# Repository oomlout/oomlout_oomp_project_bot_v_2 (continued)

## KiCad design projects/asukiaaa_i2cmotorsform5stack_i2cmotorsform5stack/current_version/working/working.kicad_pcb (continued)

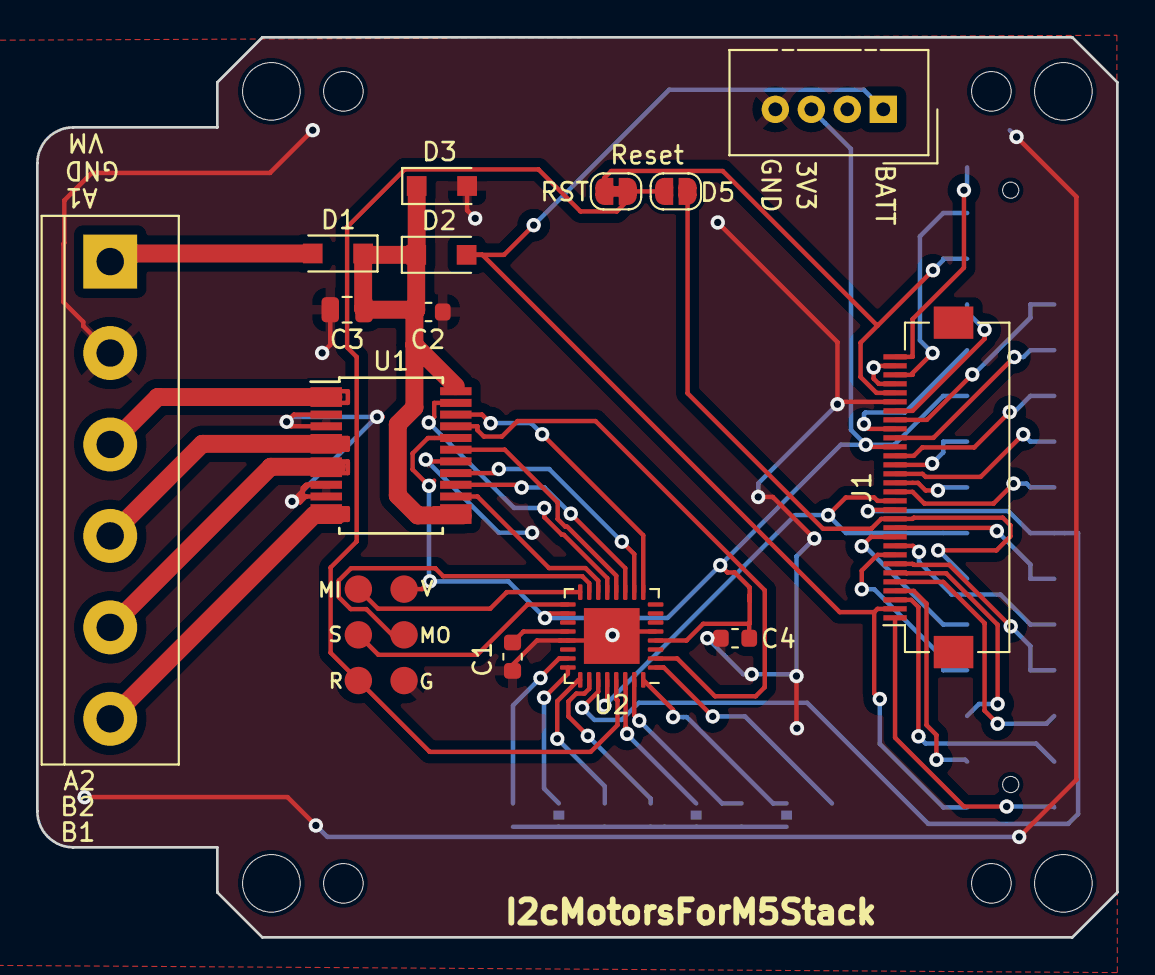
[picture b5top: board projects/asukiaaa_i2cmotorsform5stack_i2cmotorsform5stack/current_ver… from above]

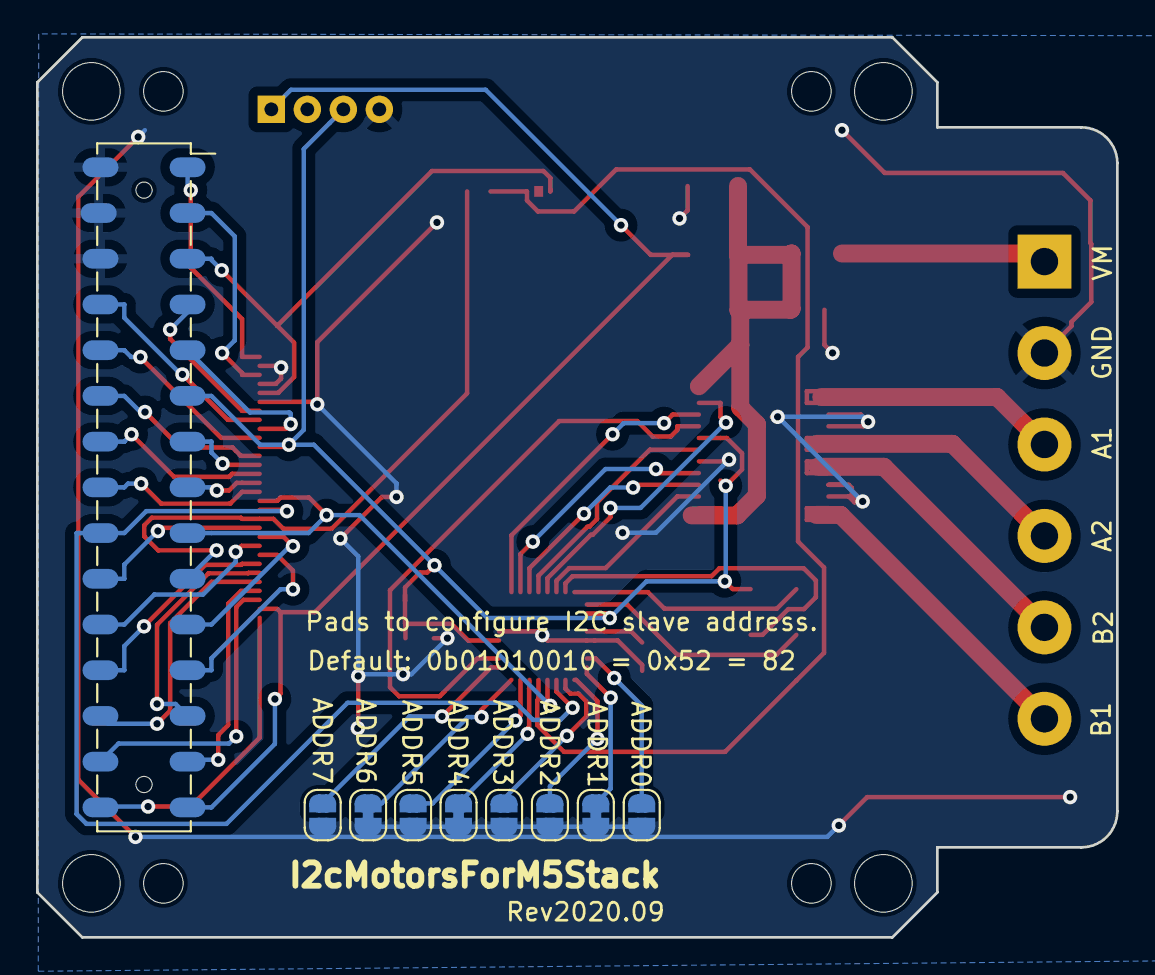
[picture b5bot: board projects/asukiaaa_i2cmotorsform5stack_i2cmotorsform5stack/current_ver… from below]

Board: 2 copper layers, 60.0 x 50.0 mm, 32 parts (9 on the bottom side), 54 nets.

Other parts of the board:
REF1, REF4, REF6, REF9: MountingHole_3.2mm_M3
REF2, REF3, REF7, REF8: MountingHole_2.2mm_M2

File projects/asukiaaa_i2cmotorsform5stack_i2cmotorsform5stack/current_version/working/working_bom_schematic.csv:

"Source:","C:\gh\oomlout_oomp_project_bot_v_2\projects\asukiaaa_i2cmotorsform5stack_i2cmotorsform5stack\current_version\working\working.kicad_sch"
"Date:","25/09/2023 20:22:21"
"Tool:","Eeschema 7.0.6"
"Generator:","C:/Program Files/KiCad/7.0/bin/scripting/plugins/bom_csv_grouped_by_value_with_fp.py"
"Component Count:","24"
"Ref","Qnty","Value","Cmp name","Footprint","Description","Vendor","DNP"
"ADDR0, ADDR2, ADDR3, ADDR5, ADDR7","5","NO","Jumper_NO_Small-Device-I2cMotorsForM5Stack-rescue","Jumper:SolderJumper-2_P1.3mm_Open_RoundedPad1.0x1.5mm","","",""
"ADDR1, ADDR4, ADDR6","3","NC","Jumper_NC_Small-Device-I2cMotorsForM5Stack-rescue","Jumper:SolderJumper-2_P1.3mm_Bridged_RoundedPad1.0x1.5mm","","",""
"C1, C2, C4","3","0.1uf","C","Capacitor_SMD:C_0603_1608Metric","Unpolarized capacitor","",""
"C3","1","10uf","C","Capacitor_SMD:C_0805_2012Metric","Unpolarized capacitor","",""
"D1, D2, D3","3","D","D","Diode_SMD:D_SOD-123F","Diode","",""
"J1","1","FFC_connector","Conn_02x15_Odd_Even","Connector_FFC-FPC:Hirose_FH12-30S-0.5SH_1x30-1MP_P0.50mm_Horizontal","Generic connector, double row, 02x15, odd/even pin numbering scheme (row 1 odd numbers, row 2 even numbers), script generated (kicad-library-utils/schlib/autogen/connector/)","",""
"J2","1","2x15socket","Conn_02x15_Odd_Even","my-kicad-footprints:PinSocket_2x15_P2.54mm_Vertical_SMD_just_for_M5Stack_bottom","Generic connector, double row, 02x15, odd/even pin numbering scheme (row 1 odd numbers, row 2 even numbers), script generated (kicad-library-utils/schlib/autogen/connector/)","",""
"J3","1","Conn_01x06","Conn_01x06","footprints:2x03_P2.54mm_Pads","Generic connector, single row, 01x06, script generated (kicad-library-utils/schlib/autogen/connector/)","",""
"J4","1","Conn_01x06","Conn_01x06","TerminalBlock:TerminalBlock_bornier-6_P5.08mm","Generic connector, single row, 01x06, script generated (kicad-library-utils/schlib/autogen/connector/)","",""
"J5","1","Conn_01x04","Conn_01x04","Connector:NS-Tech_Grove_1x04_P2mm_Vertical","Generic connector, single row, 01x04, script generated (kicad-library-utils/schlib/autogen/connector/)","",""
"JP1","1","NC","Jumper_NC_Small-Device-I2cMotorsForM5Stack-rescue","Jumper:SolderJumper-2_P1.3mm_Bridged_RoundedPad1.0x1.5mm","","",""
"JP2","1","NO","Jumper_NO_Small-Device-I2cMotorsForM5Stack-rescue","Jumper:SolderJumper-2_P1.3mm_Open_RoundedPad1.0x1.5mm","","",""
"U1","1","TB6612FNG","TB6612FNG-Driver_Motor-I2cMotorsForM5Stack-rescue","Package_SO:SSOP-24_5.3x8.2mm_P0.65mm","","",""
"U2","1","ATmega328PB-MU","ATmega328PB-MU-MCU_Microchip_ATmega-I2cMotorsForM5Stack-rescue","Package_DFN_QFN:QFN-32-1EP_5x5mm_P0.5mm_EP3.1x3.1mm","","",""

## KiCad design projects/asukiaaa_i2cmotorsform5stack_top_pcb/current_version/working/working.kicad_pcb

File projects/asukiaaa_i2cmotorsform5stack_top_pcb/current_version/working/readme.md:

# i2cmotorsform5stack
 
## summary 
* id: asukiaaa_i2cmotorsform5stack_top_pcb
* user: asukiaaa
* name: i2cmotorsform5stack
* board: top_pcb
* repo: https://github.com/asukiaaa/I2cMotorsForM5Stack
* src_file_repo_kicad_pcb: top_pcb/top_pcb.kicad_pcb
* src_file_repo_kicad_pcb_link: https://github.com/asukiaaa/I2cMotorsForM5Stack/tree/master/top_pcb/top_pcb.kicad_pcb

* src_file_repo_sch: top_pcb/top_pcb.sch
* src_file_repo_sch_link: https://github.com/asukiaaa/I2cMotorsForM5Stack/tree/master/top_pcb/top_pcb.sch
* full details link: https://github.com/oomlout/oomlout_oomp_project_bot_v_2/tree/main/projects/asukiaaa_i2cmotorsform5stack_top_pcb/current_version/working  

## schematic  
  
[schematic (pdf)](working_schematic.pdf) 

## pcb  

[board (pdf)](working.pdf)  

## working_bom
| Id | Designator | Footprint | Quantity | Designation | Supplier and ref |  | None | 
| --- | --- | --- | --- | --- | --- | --- | --- | 
| 1 | J2 | PinHeader_2x15_P2.54mm_Vertical_SMD_for_M5Stack | 1 | header |  |  | [''] | 
| 2 | corner1,corner4 | corner_edge1 | 2 | corner_edge1 |  |  | [''] | 
| 3 | corner2,corner3 | corner_edge2 | 2 | corner_edge2 |  |  | [''] | 
| 4 | J3 | PinHeader_1x30_P1.27mm_Vertical_without_silks | 1 | free_holes |  |  | [''] | 
| 5 | J1 | Hirose_FH12-30S-0.5SH_1x30-1MP_P0.50mm_Horizontal | 1 | flat_cable_connector |  |  | [''] | 
| 6 | J4 | NS-Tech_Grove_1x04_P2mm_Vertical | 1 | Conn_01x04 |  |  | [''] | 

## bom_schematic
| Ref | Qnty | Value | Cmp name | Footprint | Description | Vendor | DNP | 
| --- | --- | --- | --- | --- | --- | --- | --- | 
| J1 | 1 | flat_cable_connector | Conn_02x15_Odd_Even | Connector_FFC-FPC:Hirose_FH12-30S-0.5SH_1x30-1MP_P0.50mm_Horizontal | Generic connector, double row, 02x15, odd/even pin numbering scheme (row 1 odd numbers, row 2 even numbers), script generated (kicad-library-utils/schlib/autogen/connector/) |  |  | 
| J2 | 1 | header | Conn_02x15_Odd_Even | footprints:PinHeader_2x15_P2.54mm_Vertical_SMD_for_M5Stack | Generic connector, double row, 02x15, odd/even pin numbering scheme (row 1 odd numbers, row 2 even numbers), script generated (kicad-library-utils/schlib/autogen/connector/) |  |  | 
| J3 | 1 | free_holes | Conn_02x15_Odd_Even | footprints:PinHeader_1x30_P1.27mm_Vertical_without_silks | Generic connector, double row, 02x15, odd/even pin numbering scheme (row 1 odd numbers, row 2 even numbers), script generated (kicad-library-utils/schlib/autogen/connector/) |  |  | 
| J4 | 1 | Conn_01x04 | Conn_01x04 | Connector:NS-Tech_Grove_1x04_P2mm_Vertical | Generic connector, single row, 01x04, script generated (kicad-library-utils/schlib/autogen/connector/) |  |  |

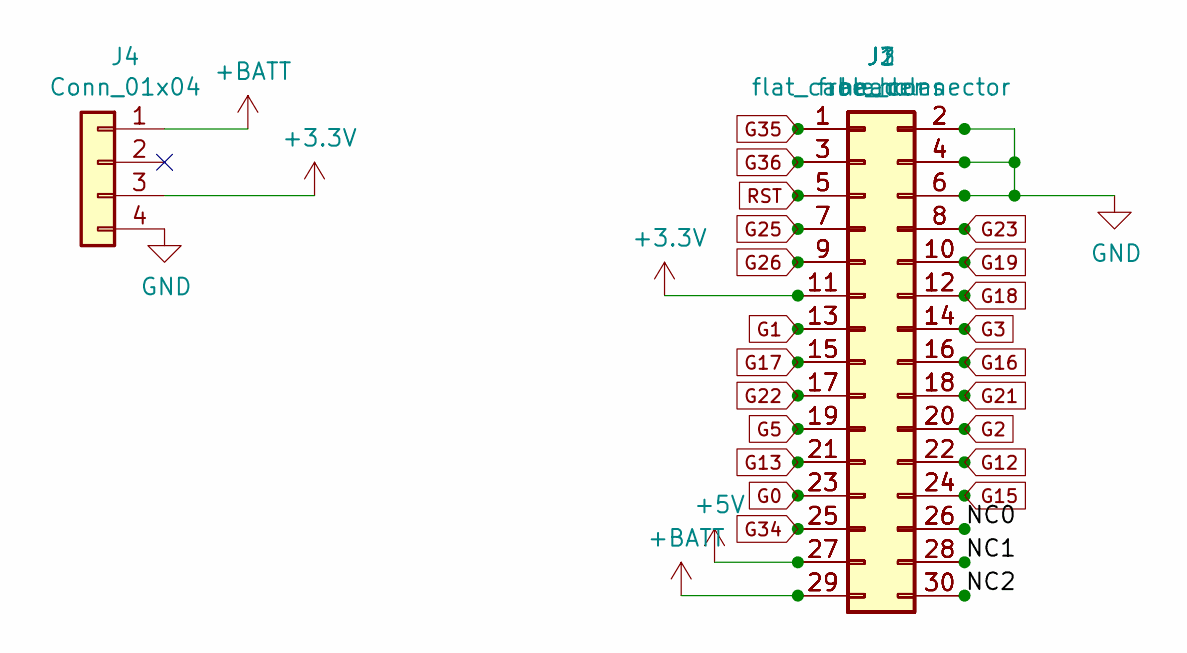
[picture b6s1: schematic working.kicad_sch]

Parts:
J1: flat_cable_connector; Hirose_FH12-30S-0.5SH_1x30-1MP_P0.50mm_Horizontal
J2: header; PinHeader_2x15_P2.54mm_Vertical_SMD_for_M5Stack
J3: free_holes; PinHeader_1x30_P1.27mm_Vertical_without_silks
J4: Conn_01x04; NS-Tech_Grove_1x04_P2mm_Vertical

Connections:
+3V3: J1.11, J2.11, J3.11, J4.3
+5V: J1.27, J2.27, J3.27
+BATT: J1.29, J2.29, J3.29, J4.1
/NC0: J1.26, J2.26, J3.26
/NC1: J1.28, J2.28, J3.28
/NC2: J1.30, J2.30, J3.30
G0: J1.23, J2.23, J3.23
G1: J1.13, J2.13, J3.13
G2: J1.20, J2.20, J3.20
G3: J1.14, J2.14, J3.14
G5: J1.19, J2.19, J3.19
G12: J1.22, J2.22, J3.22
G13: J1.21, J2.21, J3.21
G15: J1.24, J2.24, J3.24
G16: J1.16, J2.16, J3.16
G17: J1.15, J2.15, J3.15
G18: J1.12, J2.12, J3.12
G19: J1.10, J2.10, J3.10
G21: J1.18, J2.18, J3.18
G22: J1.17, J2.17, J3.17
G23: J1.8, J2.8, J3.8
G25: J1.7, J2.7, J3.7
G26: J1.9, J2.9, J3.9
G34: J1.25, J2.25, J3.25
G35: J1.1, J2.1, J3.1
G36: J1.3, J2.3, J3.3
GND: J1.2, J1.4, J1.6, J2.2, J2.4, J2.6, J3.2, J3.4, J3.6, J4.4
RST: J1.5, J2.5, J3.5

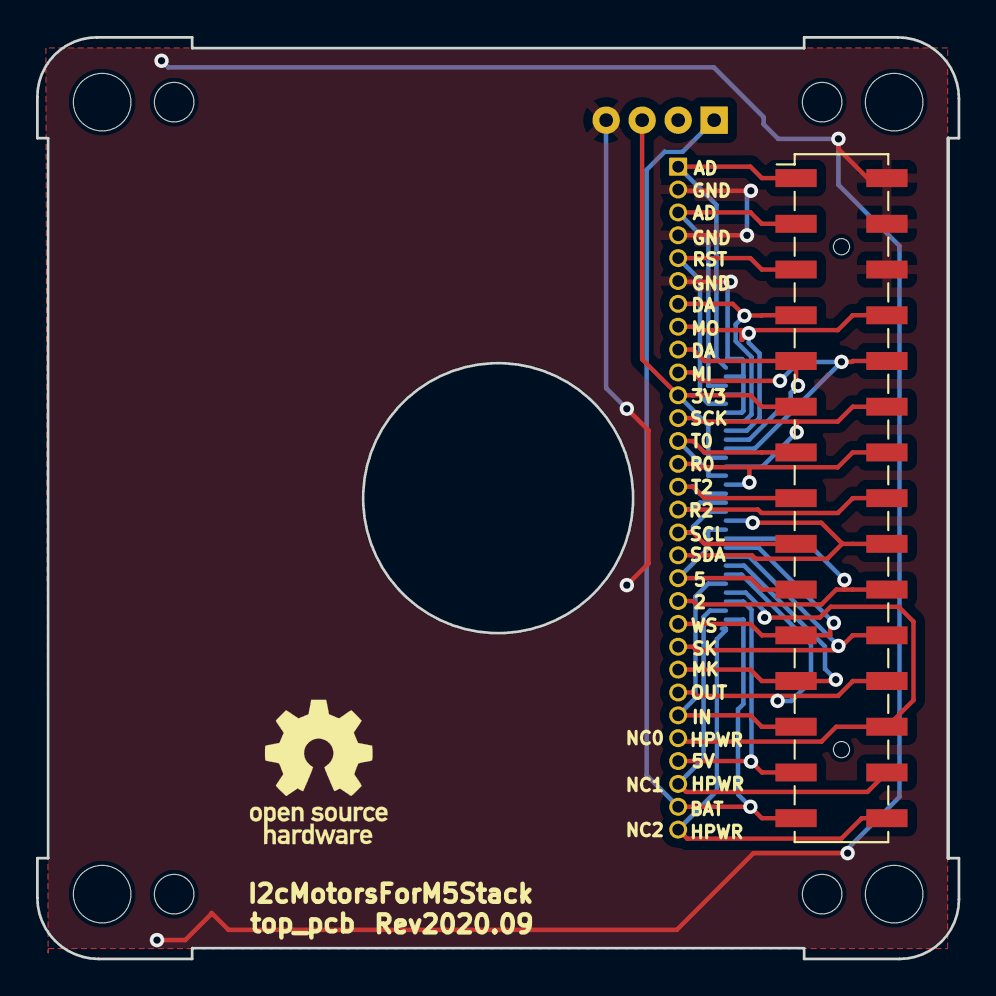
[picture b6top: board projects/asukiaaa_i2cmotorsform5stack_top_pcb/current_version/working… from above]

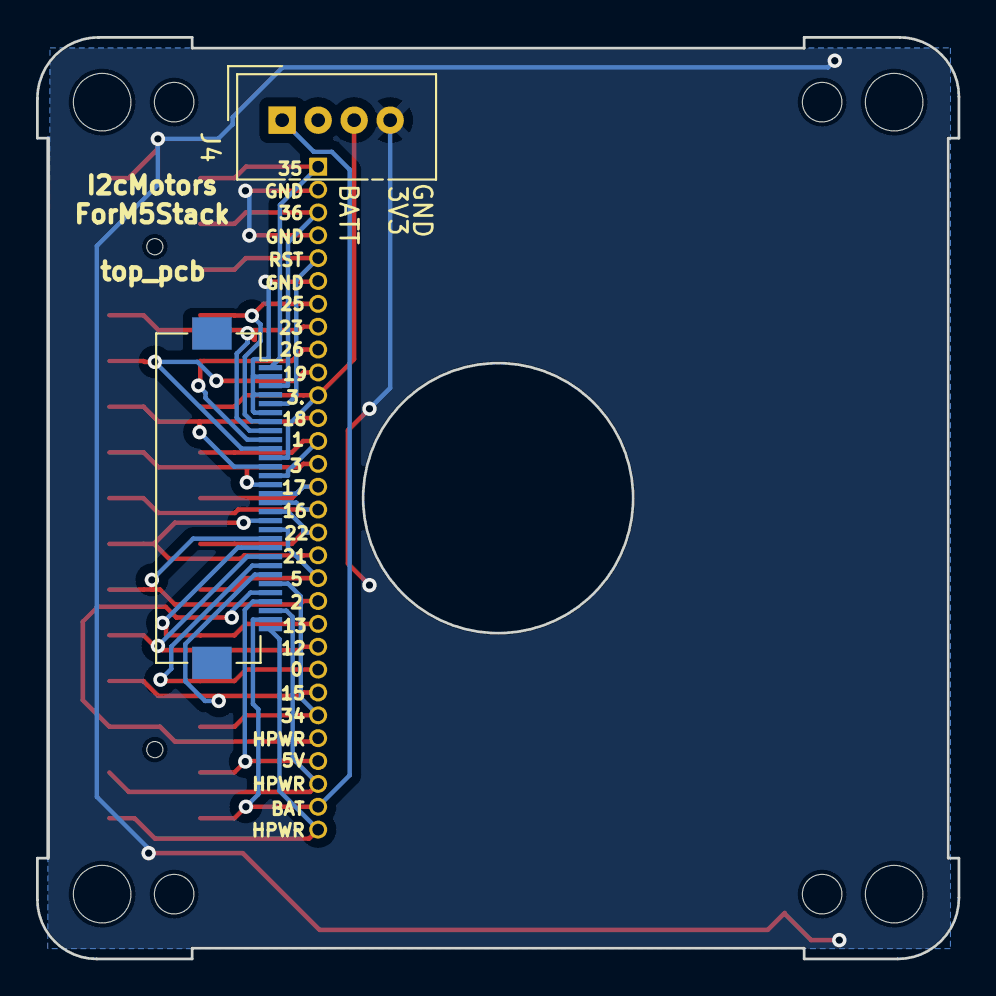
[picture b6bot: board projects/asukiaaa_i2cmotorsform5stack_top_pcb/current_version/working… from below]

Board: 2 copper layers, 51.2 x 51.2 mm, 17 parts (2 on the bottom side), 28 nets.

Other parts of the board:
OSHWREF2: OSHW-Logo_7.5x8mm_SilkScreen
REF1, REF4, REF6, REF9: MountingHole_3.2mm_M3
REF2, REF3, REF7, REF8: MountingHole_2.2mm_M2
corner1, corner4: corner_edge1
corner2, corner3: corner_edge2
